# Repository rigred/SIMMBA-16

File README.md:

# SIMMBA-16. P
Open-source 30 pins 16MB SIMM memory module

## Status Updates
* 2022-06-12
  * Version 1A assembled and tested [link](https://twitter.com/0xCats/status/1524708654913662977)
* Many months of happily using rev A1 board
* 2022-11-22
  * Version 2A released to the public
* 2023-01-17
  * Added Filthy WIP autorouted Rev. B1 (16MB with Parity) and A11 pullup

# Just gimme the Gerbers!
[gerber.zip](https://raw.githubusercontent.com/rigred/SIMMBA-16/main/production/gerber.zip)

# Ordering specifics:
 * 1.2mm Thickness
 * HASL or ENIG (any finish is fine)

# Why?
Because I have a 486 motherboard that I'm quite fond of that featured a mix of 2x72pin and 4x30pin SIMM sockets.
I wanted to use both at maximum capacity. Also 30 pin SIMM memory prices are not great.

# What is this thing?
A 16MB(the absolute limit) 30 pin SIMM/SIPP Memory module for various PC compatibles.
This board was designed to be as low cost and simple as possible and supports flexibility in ram chip and socket selection.

## Supported RAM chips

3.3V chips may be relatively easily found from cheaply available 256MB EDO DIMM's.

These are by far the preferred choice in comparison to the now rarer 5V chips.

I have tested and validated some of the below chips and found them to be 5V IO tolerant in use despite manufacturer data sheets not directly ascribing such.

Of these the Micron chips are by far the most common and robust. All others have been data sheet checked to be electrically compatible.

## (3.3V)
 * MT4LC16M4H9 (Preferred, Tested & Validated)
 * GM71V65403C (Tested)
 * K4F640412C (Validated)
 * KM44V16104BK (Validated)
## (5V)
 * KM44C16100BK
 * K4E660411C
 * K4F640411B

# Assembly

## Bill of Materials

[HTML BOM](https://htmlpreview.github.io/?https://raw.githubusercontent.com/rigred/SIMMBA-16/main/bom/ibom.html)

## RAM Salvaging
If you are not using new-old-stock chips and are instead salvaging compatible chips form DRAM Modules then I recommend you take the utmost care in desoldering such.
* If possible test your source RAM boards before salvaging, you do not want to be taking risks with unknown quality chips.
* It is very easy to overheat and destroy these old DRAM chips, use a preheater and hot air station or temperature controlled reflow oven to remove the chips
* If you have not done this before, expect mysery pain and failure, but don't give up.
* I bear absolutely no responsibility for any of this should it go horribly wrong.

## Voltage selection
* When 3.3V chips are used it is required to install a suitable 3.3V LDO regulator such as the common AMS1117-3.3 as well as the 10uF Capacitor
* When 5V chips are used you must bridge the indicated pads with a 0-Ohm resistor or suitable piece of metal and install the 22uF Capacitor
* _DO NOT_ install the 3.3V Regulator when using 5V chips and bridging the indicated pads.

## EDO / FPM selection
For the most part only the FPM bridge should be populated. In this mode the CAS signal is tied to the Output Enable signal pin of the chips.
On EDO DRAM chips this forces the output buffers to become invalid and cleared as soon as the CAS is toggled and allows EDO chips to behave like FPM chips.
In rare cases you may want to configure this module as EDO mode, such as in use with 72pin to 4x30pin SIMM-Saver/SIMM-Expander boards.

## SIPP mode
If you wish to use these as SIPP modules, in case say your SIMM sockets are broken, or you've found some very obscure motherboard that both supports SIPP memory and this size of module. Then you can simply solder a right angle 100mil/2.54mm header to the holes along the edge.

# Soldering
* For repeatable good results when soldering the ram chips in place it is recommended to use a stencil and soldering paste and soldering the whole board in one pass on a hot plate.
* Hand soldering is possible but great care must be taken to ensure good contact on the pads and no solder bridging. *Large quantities of flux recommended.*

# Troubleshooting

1) If you are using the 3.3V regulator design and are experiencing voltage instability it may be necessary to adjust the capacitance of the 5V input and 3.3V output filter capacitors.
  * In this design, less can often be better.

2) After assembly it is recommended to first power test and check your handiwork in expectation of failure. Feel for any hot parts on the DRAM

3) If you are getting memory errors there is a good chance that either some pins are not making good contact or you've overheated one of the chips.

4) Mixing and matching these modules with other modules in the same bank is _NOT_ supported nor recommended.

# Revision A1 testing

The A1 revision SIMMBA module assembled

64MB of SIMMBA A1 revision under test

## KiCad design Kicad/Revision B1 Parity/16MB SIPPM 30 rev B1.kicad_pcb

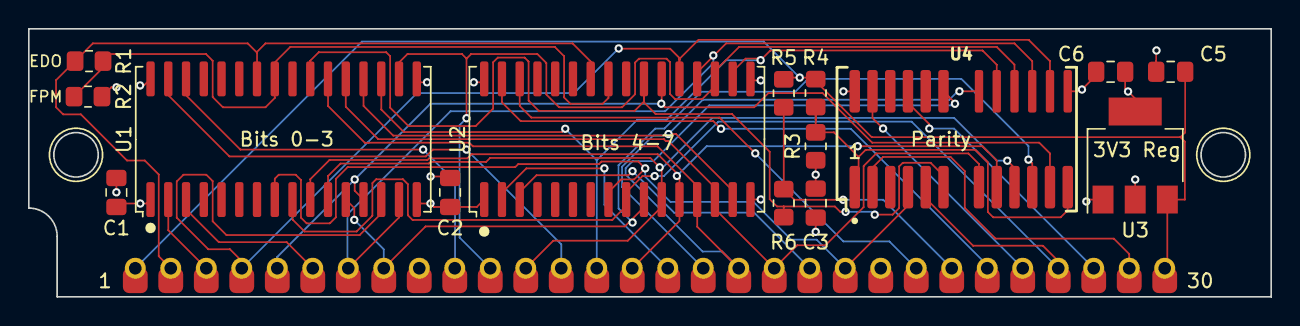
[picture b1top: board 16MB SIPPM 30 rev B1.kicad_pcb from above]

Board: 4 copper layers, 88.9 x 19.2 mm, 16 parts (0 on the bottom side), 32 nets.

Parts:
C1, C2, C3: 220nF; C_0805_2012Metric_Pad1.18x1.45mm_HandSolder
C5: 22uF; C_0805_2012Metric_Pad1.18x1.45mm_HandSolder
C6: 10uF; C_0805_2012Metric_Pad1.18x1.45mm_HandSolder
J1: SIMM-30; SIPP_30_A2
R1: FPM; R_0805_2012Metric_Pad1.20x1.40mm_HandSolder
R2: EDO; R_0805_2012Metric_Pad1.20x1.40mm_HandSolder
R3, R4, R6: 0; R_0805_2012Metric_Pad1.20x1.40mm_HandSolder
R5: 10K; R_0805_2012Metric_Pad1.20x1.40mm_HandSolder
U1, U2: MT4LC16M4H9; SOJ-32_10.16x21.50mm_P1.27mm
U3: AMS1117-3.3; SOT-223-3_TabPin2
U4: HM5116100S; SOJ-26_300mil

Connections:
+3V3: C1.1, C2.1, C3.1, C6.1, R3.1, U1.1 (VDD), U1.16 (VDD), U2.1 (VDD), U2.16 (VDD), U3.2 (VO)
+5V: C5.1, J1.1 (+5V), J1.30 (+5V), R4.2, R5.1, U3.3 (VI)
/2A0: J1.8 (A3), U1.12 (A2), U2.10 (A0), U4.11 (A2)
/2A1: J1.12 (A5), U1.11 (A1), U2.11 (A1), U4.10 (A1)
/2A2: J1.15 (A7), U1.10 (A0), U2.12 (A2), U4.9 (A0)
/2A3: J1.18 (A9), U1.22 (A10), U2.13 (A3), U4.21 (A9)
/2A4: J1.19 (A10), U1.21 (A9), U2.14 (A4), U4.8 (A10)
/2A5: J1.17 (A8), U1.20 (A8), U2.15 (A5), U4.19 (A8)
/2A6: J1.14 (A6), U1.19 (A7), U2.18 (A6), U4.18 (A7)
/2A7: J1.11 (A4), U1.18 (A6), U2.19 (A7), U4.17 (A6)
/2A8: J1.7 (A2), U1.15 (A5), U2.20 (A8), U4.16 (A5)
/2A9: J1.4 (A0), U1.14 (A4), U2.21 (A9), U4.15 (A4)
/2A10: J1.5 (A1), U1.13 (A3), U2.22 (A10), U4.12 (A3)
/2A11: R6.2, U1.23 (A11), U2.23 (A11), U4.6 (A11)
/DP: J1.29 (DP_IN), U4.2 (DIN)
/DQ0: J1.3 (DQ0), U1.2 (DQ0)
/DQ1: J1.6 (DQ1), U1.3 (DQ1)
/DQ2: J1.10 (DQ2), U1.30 (DQ2)
/DQ3: J1.13 (DQ3), U1.31 (DQ3)
/DQ4: J1.16 (DQ4), U2.2 (DQ0)
/DQ5: J1.20 (DQ5), U2.3 (DQ1)
/DQ6: J1.23 (DQ6), U2.30 (DQ2)
/DQ7: J1.25 (DQ7), U2.31 (DQ3)
/QP: J1.26 (DP_OUT), U4.25 (DOUT)
/SIMM_A11: J1.24 (A11), R5.2, R6.1
/VDD_PAR: R3.2, R4.1, U4.1 (+5V), U4.13 (+5V)
/~CASP: J1.28 (~CASP), U4.23 (/CAS)
/~CAS: J1.2 (~CAS), R1.1, U1.26 (/CAS), U2.26 (/CAS)
/~OE: R1.2, R2.1, U1.25 (/OE), U2.25 (/OE)
/~RAS: J1.27 (~RAS), U1.9 (/RAS), U2.9 (/RAS), U4.5 (/RAS)
/~WE: J1.21 (~WE), U1.8 (/WE), U2.8 (/WE), U4.4 (/WE)
GND: C1.2, C2.2, C3.2, C5.2, C6.2, J1.9 (GND), J1.22 (GND), R2.2, U1.17 (VSS), U1.32 (VSS), U2.17 (VSS), U2.32 (VSS), U3.1 (GND), U4.14 (VSS), U4.26 (VSS)

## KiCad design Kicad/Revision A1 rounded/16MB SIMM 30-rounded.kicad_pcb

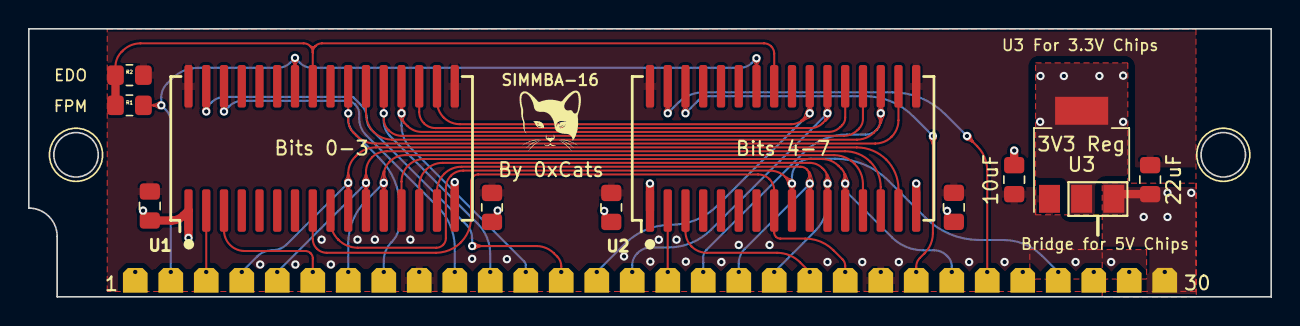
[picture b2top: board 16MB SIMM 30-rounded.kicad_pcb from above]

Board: 2 copper layers, 88.9 x 19.2 mm, 12 parts (0 on the bottom side), 27 nets.

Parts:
C1, C2, C3, C4: 220nF; C_0805_2012Metric_Pad1.18x1.45mm_HandSolder
C5: 22uF; C_0805_2012Metric_Pad1.18x1.45mm_HandSolder
C6: 10uF; C_0805_2012Metric_Pad1.18x1.45mm_HandSolder
J1: SIMM-30; SIMM_30
R1: FPM; R_0805_2012Metric_Pad1.20x1.40mm_HandSolder
R2: EDO; R_0805_2012Metric_Pad1.20x1.40mm_HandSolder
U1, U2: MT4LC16M4H9; SOJ-32_400mil
U3: AMS1117-3.3; SOT-223-3_TabPin2

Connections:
+5V: C5.1, J1.1 (+5V), J1.30 (+5V), U3.3 (VI)
/2A0: J1.18 (A9), U1.15 (A5), U2.10 (A0)
/2A1: J1.19 (A10), U1.14 (A4), U2.11 (A1)
/2A2: J1.24 (A11), U1.13 (A3), U2.12 (A2)
/2A3: J1.7 (A2), U1.12 (A2), U2.13 (A3)
/2A4: J1.5 (A1), U1.11 (A1), U2.14 (A4)
/2A5: J1.4 (A0), U1.10 (A0), U2.15 (A5)
/2A6: J1.8 (A3), U1.23 (A11), U2.18 (A6)
/2A7: J1.17 (A8), U1.22 (A10), U2.19 (A7)
/2A8: J1.11 (A4), U1.21 (A9), U2.20 (A8)
/2A9: J1.12 (A5), U1.20 (A8), U2.21 (A9)
/2A10: J1.15 (A7), U1.19 (A7), U2.22 (A10)
/2A11: J1.14 (A6), U1.18 (A6), U2.23 (A11)
/DQ0: J1.3 (DQ0), U1.2 (DQ0)
/DQ1: J1.6 (DQ1), U1.3 (DQ1)
/DQ2: J1.10 (DQ2), U1.30 (DQ2)
/DQ3: J1.13 (DQ3), U1.31 (DQ3)
/DQ4: J1.16 (DQ4), U2.2 (DQ0)
/DQ5: J1.20 (DQ5), U2.3 (DQ1)
/DQ6: J1.23 (DQ6), U2.30 (DQ2)
/DQ7: J1.25 (DQ7), U2.31 (DQ3)
/~CAS: J1.2 (~CAS), R1.1, U1.26 (/CAS), U2.26 (/CAS)
/~OE: R1.2, R2.1, U1.25 (/OE), U2.25 (/OE)
/~RAS: J1.27 (~RAS), U1.9 (/RAS), U2.9 (/RAS)
/~WE: J1.21 (~WE), U1.8 (/WE), U2.8 (/WE)
GND: C1.2, C2.2, C3.2, C4.2, C5.2, C6.2, J1.9 (GND), J1.22 (GND), R2.2, U1.17 (VSS), U1.32 (VSS), U2.17 (VSS), U2.32 (VSS), U3.1 (GND)
VDD: C1.1, C2.1, C3.1, C4.1, C6.1, U1.1 (VDD), U1.16 (VDD), U2.1 (VDD), U2.16 (VDD), U3.2 (VO)

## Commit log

2022-11-21 First upload of 16MB SIMMBA rev A2
2022-11-21 Add Rev A2 SIPPM images
2022-11-21 cleanup old items
2022-11-21 fixed pads missing on back layer
2022-11-21 update images to fixed rev A2 with correct pads
2022-11-22 add initial project readme
2022-11-22 fix relative image paths
2022-11-22 fix image names for gh markdown
2022-11-22 Images plz
2022-11-22 image names fixed to no spaces
2022-11-22 spellchecked
2022-11-22 interactive html bom added
2022-11-22 revert to using htmlpreview.github.io
2022-11-22 update bom to A2
2022-11-22 indent fixes
2022-11-22 late night-morning edits
2022-11-22 spacing - new lines
2022-11-22 remove redundant images
2023-01-17 * Adds rough 16MB with parity variant
    Cleaned up Project structure and placed boards into Kicad/<Revisions>
    directories
2023-01-17 Incorporate README changes
2023-01-17 Update to reflect changes for B1 Rev
2023-01-17 minor Rev B1 cleanups - not prod ready

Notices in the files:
parts and their libraries:
License: Licensed under the TAPR Open Hardare License (www.tapr.org/OHL)
